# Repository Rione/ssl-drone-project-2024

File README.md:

# ssl-drone-project-2024

## branch tree
```
master{
    development{
        dp_KiCad{}
        dp_Fusion360{}
        dp_software{
            dp_stm32{}
            dp_esp32{}
        }
    }
}
```

Githubにコミットするときは基本的に``dp_*****``ブランチを選択

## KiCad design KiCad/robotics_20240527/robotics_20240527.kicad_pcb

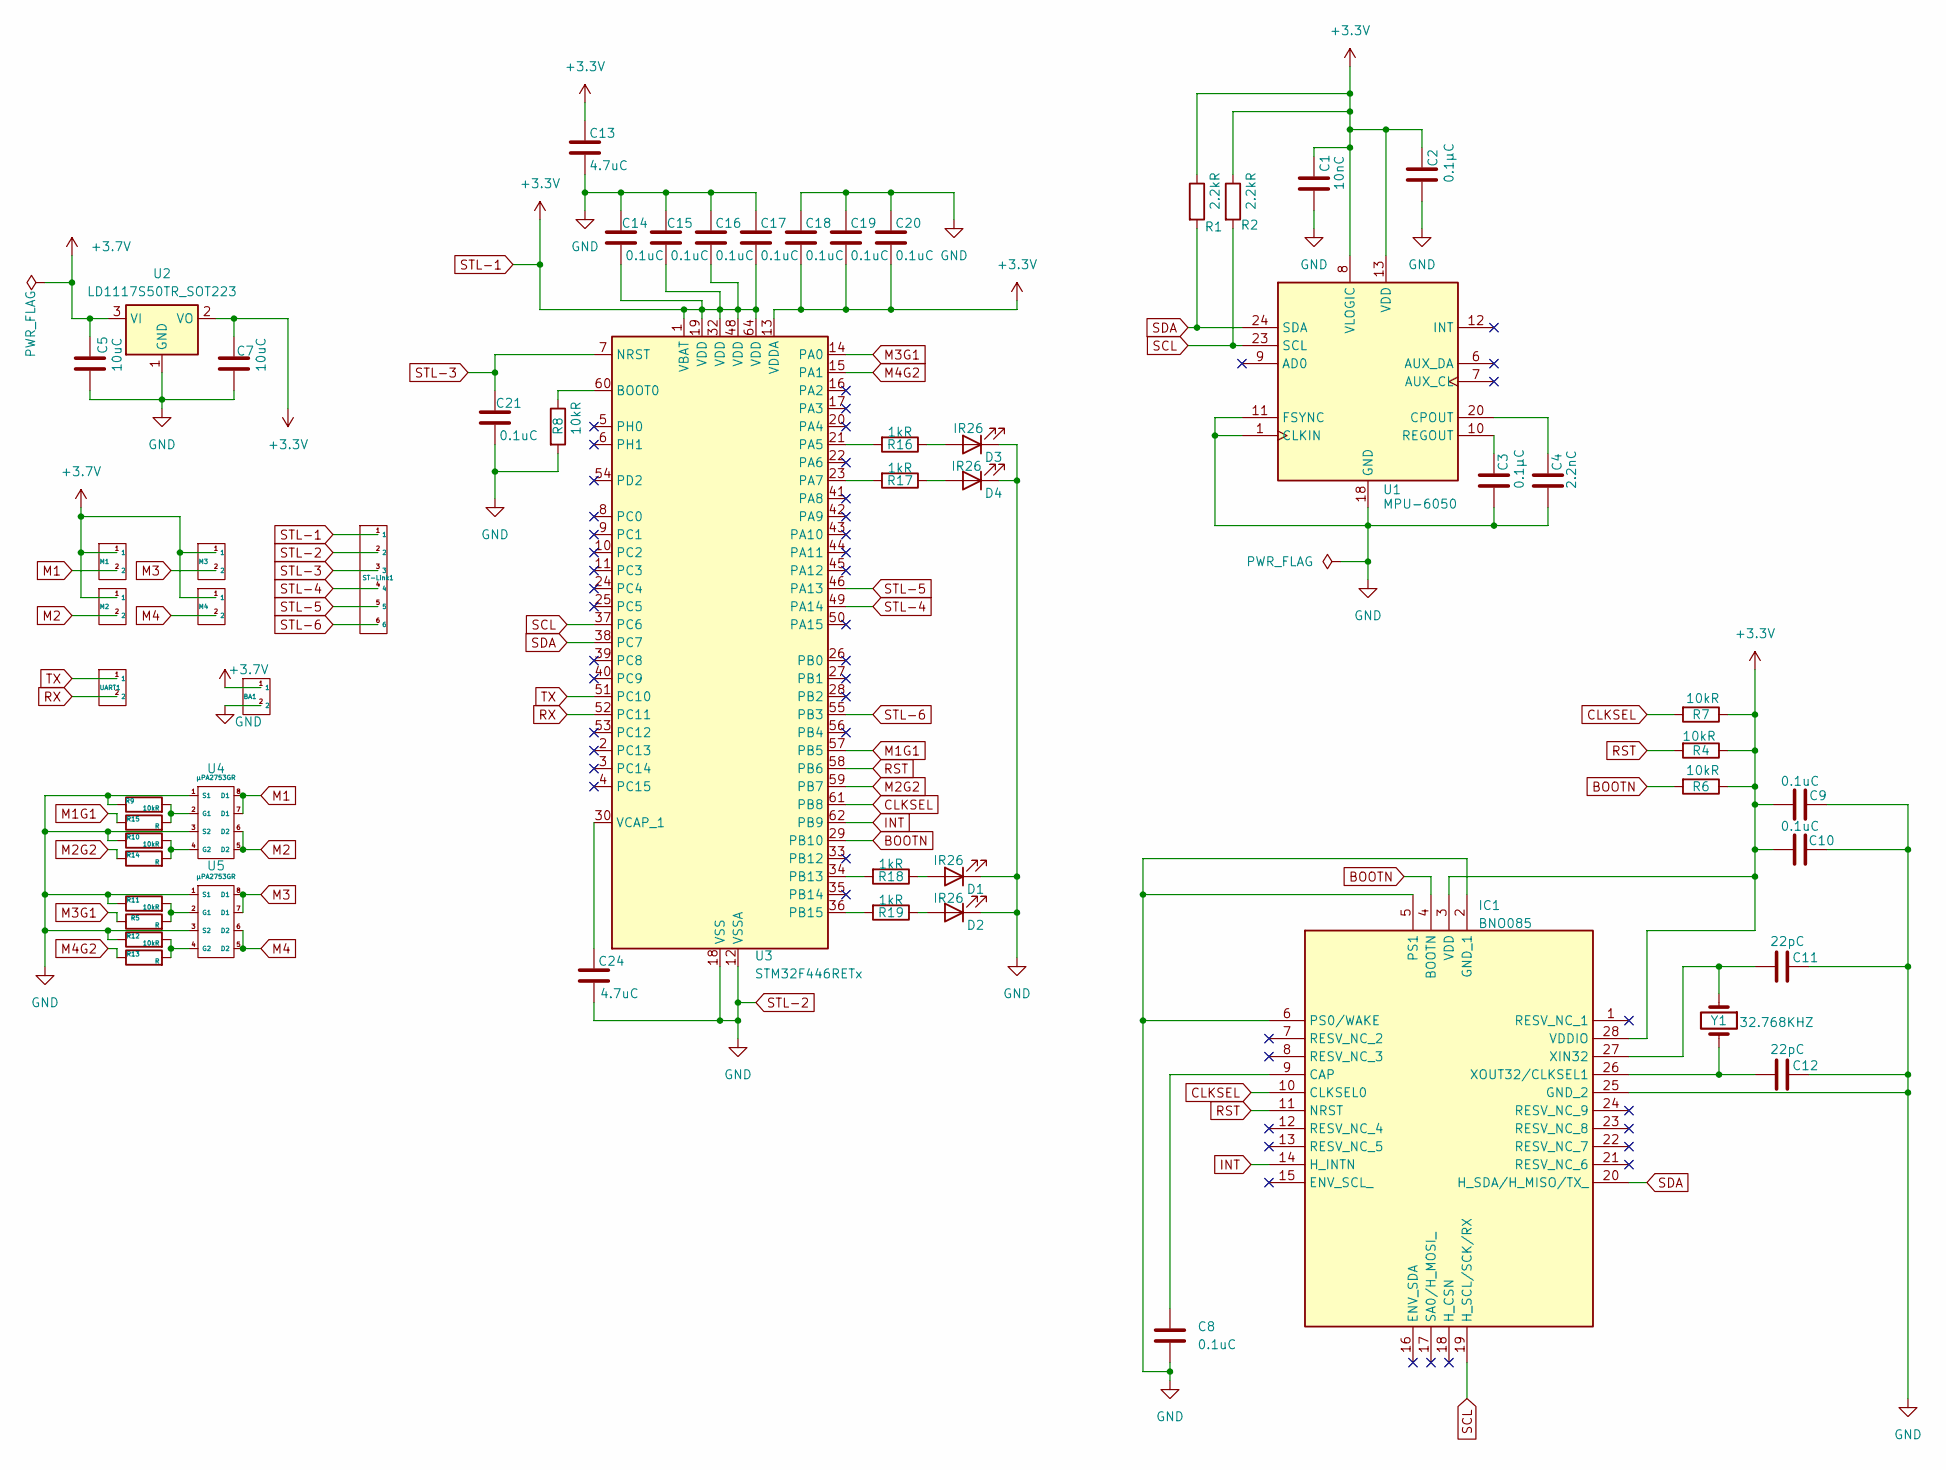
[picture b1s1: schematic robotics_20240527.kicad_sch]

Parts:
BA1: JST_PH_B2B-PH-K_1x02_P2.00mm_Vertical
C1: 10nC; C_0603_1608Metric_Pad1.08x0.95mm_HandSolder
C2, C3: 0.1µC; C_0603_1608Metric_Pad1.08x0.95mm_HandSolder
C4: 2.2nC; C_0603_1608Metric_Pad1.08x0.95mm_HandSolder
C5, C7: 10uC; C_0603_1608Metric_Pad1.08x0.95mm_HandSolder
C8, C9, C10, C14, C15, C16, C17, C18, C19, C20, C21: 0.1uC; C_0603_1608Metric_Pad1.08x0.95mm_HandSolder
C11, C12: 22pC; C_0603_1608Metric_Pad1.08x0.95mm_HandSolder
C13, C24: 4.7uC; C_0603_1608Metric_Pad1.08x0.95mm_HandSolder
D1, D2, D3, D4: IR26; LED_1206_3216Metric
IC1: BNO085; Mouser Part Number 526-BNO085
M1, M2, M3, M4: JST_PH_B2B-PH-K_1x02_P2.00mm_Vertical
R1, R2: 2.2kR; R_0603_1608Metric_Pad0.98x0.95mm_HandSolder
R4, R6, R7, R8, R9, R10, R11, R12: 10kR; R_0603_1608Metric_Pad0.98x0.95mm_HandSolder
R5, R13, R14, R15: R; R_0603_1608Metric_Pad0.98x0.95mm_HandSolder
R16, R17, R18, R19: 1kR; R_0603_1608Metric_Pad0.98x0.95mm_HandSolder
ST-Link1: JST_PH_S6B-PH-K_1x06_P2.00mm_Horizontal
U1: MPU-6050; InvenSense_QFN-24_4x4mm_P0.5mm
U2: LD1117S50TR_SOT223; SOT-223-3_TabPin2
U3: STM32F446RETx; LQFP-64_10x10mm_P0.5mm
U4, U5: μPA2753GR; HSOP-8-1EP_3.9x4.9mm_P1.27mm_EP2.3x2.3mm
UART1: JST_PH_B2B-PH-K_1x02_P2.00mm_Vertical
Y1: 32.768KHZ; Crystal_SMD_MicroCrystal_CC7V-T1A-2Pin_3.2x1.5mm_HandSolder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

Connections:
+3.7V: BA1.1, C5.1, M1.1, M2.1, M3.1, M4.1, U2.3 (VI)
BOOTN: IC1.4 (BOOTN), R6.2, U3.29 (PB10)
CLKSEL: IC1.10 (CLKSEL0), R7.2, U3.61 (PB8)
INT: IC1.14 (H_INTN), U3.62 (PB9)
M1: M1.2, U4.7 (D1), U4.8 (D1)
M1G1: R15.1, U3.57 (PB5)
M2: M2.2, U4.5 (D2), U4.6 (D2)
M2G2: R14.1, U3.59 (PB7)
M3: M3.2, U5.7 (D1), U5.8 (D1)
M3G1: R5.1, U3.14 (PA0)
M4: M4.2, U5.5 (D2), U5.6 (D2)
M4G2: R13.1, U3.15 (PA1)
unnamed: D1.2 (A), R18.1
unnamed: D2.2 (A), R19.1
unnamed: D3.2 (A), R16.1
unnamed: D4.2 (A), R17.1
unnamed: C8.1, IC1.9 (CAP)
unnamed: C11.2, IC1.27 (XIN32), Y1.1
unnamed: C12.2, IC1.26 (XOUT32/CLKSEL1), Y1.2
unnamed: C4.1, U1.20 (CPOUT)
unnamed: C3.1, U1.10 (REGOUT)
unnamed: R8.1, U3.60 (BOOT0)
unnamed: R16.2, U3.21 (PA5)
unnamed: R17.2, U3.23 (PA7)
unnamed: R18.2, U3.34 (PB13)
unnamed: R19.2, U3.36 (PB15)
unnamed: C24.1, U3.30 (VCAP_1)
unnamed: R9.2, R15.2, U4.2 (G1)
unnamed: R10.2, R14.2, U4.4 (G2)
unnamed: R5.2, R11.2, U5.2 (G1)
unnamed: R12.2, R13.2, U5.4 (G2)
RST: IC1.11 (NRST), R4.2, U3.58 (PB6)
RX: U3.52 (PC11), UART1.2
SCL: IC1.19 (H_SCL/SCK/RX), R2.2, U1.23 (SCL), U3.37 (PC6)
SDA: IC1.20 (H_SDA/H_MISO/TX_), R1.2, U1.24 (SDA), U3.38 (PC7)
STL-1: C1.1, C2.1, C7.1, C9.2, C10.2, C13.1, C14.2, C15.2, C16.2, C17.2, C18.2, C19.2, C20.2, IC1.3 (VDD), IC1.28 (VDDIO), R1.1, R2.1, R4.1, R6.1, R7.1, ST-Link1.1, U1.8 (VLOGIC), U1.13 (VDD), U2.2 (VO), U3.1 (VBAT), U3.13 (VDDA), U3.19 (VDD), U3.32 (VDD), U3.48 (VDD), U3.64 (VDD)
STL-2: BA1.2, C1.2, C2.2, C3.2, C4.2, C5.2, C7.2, C8.2, C9.1, C10.1, C11.1, C12.1, C13.2, C14.1, C15.1, C16.1, C17.1, C18.1, C19.1, C20.1, C21.2, C24.2, D1.1 (K), D2.1 (K), D3.1 (K), D4.1 (K), IC1.2 (GND_1), IC1.5 (PS1), IC1.6 (PS0/WAKE), IC1.25 (GND_2), R8.2, R9.1, R10.1, R11.1, R12.1, ST-Link1.2, U1.1 (CLKIN), U1.11 (FSYNC), U1.18 (GND), U2.1 (GND), U3.12 (VSSA), U3.18 (VSS), U3.31 (VSS), U3.47 (VSS), U3.63 (VSS), U4.1 (S1), U4.3 (S2), U5.1 (S1), U5.3 (S2)
STL-3: C21.1, ST-Link1.3, U3.7 (NRST)
STL-4: ST-Link1.4, U3.49 (PA14)
STL-5: ST-Link1.5, U3.46 (PA13)
STL-6: ST-Link1.6, U3.55 (PB3)
TX: U3.51 (PC10), UART1.1

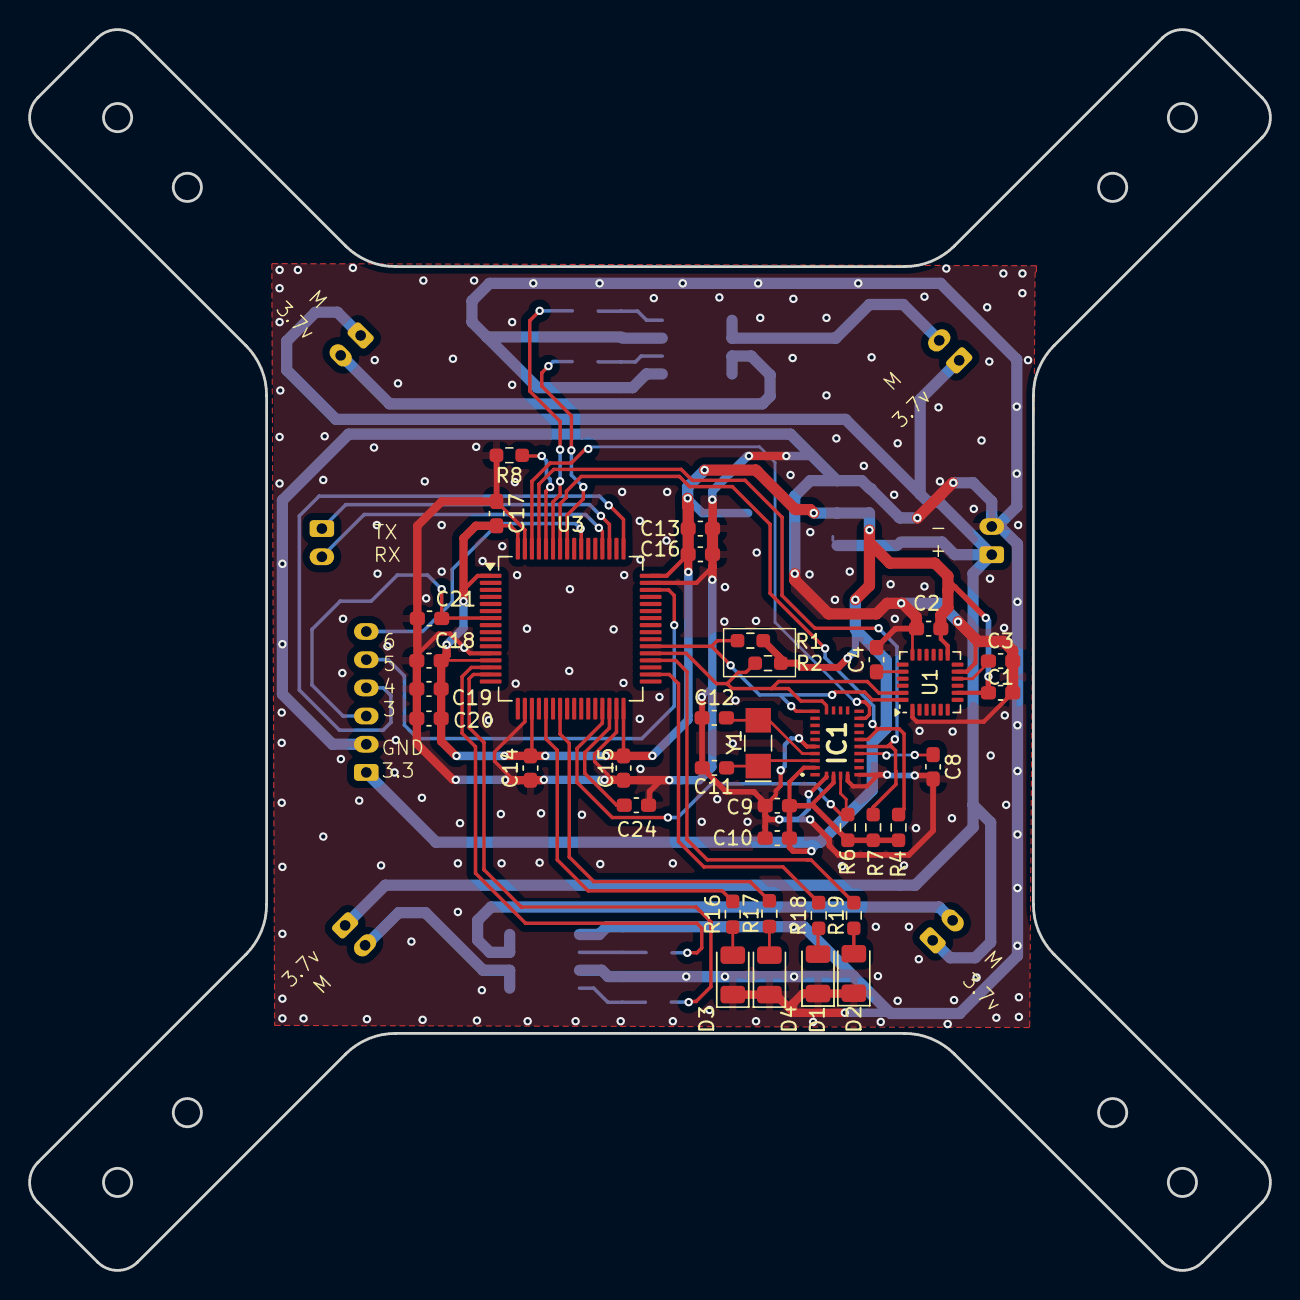
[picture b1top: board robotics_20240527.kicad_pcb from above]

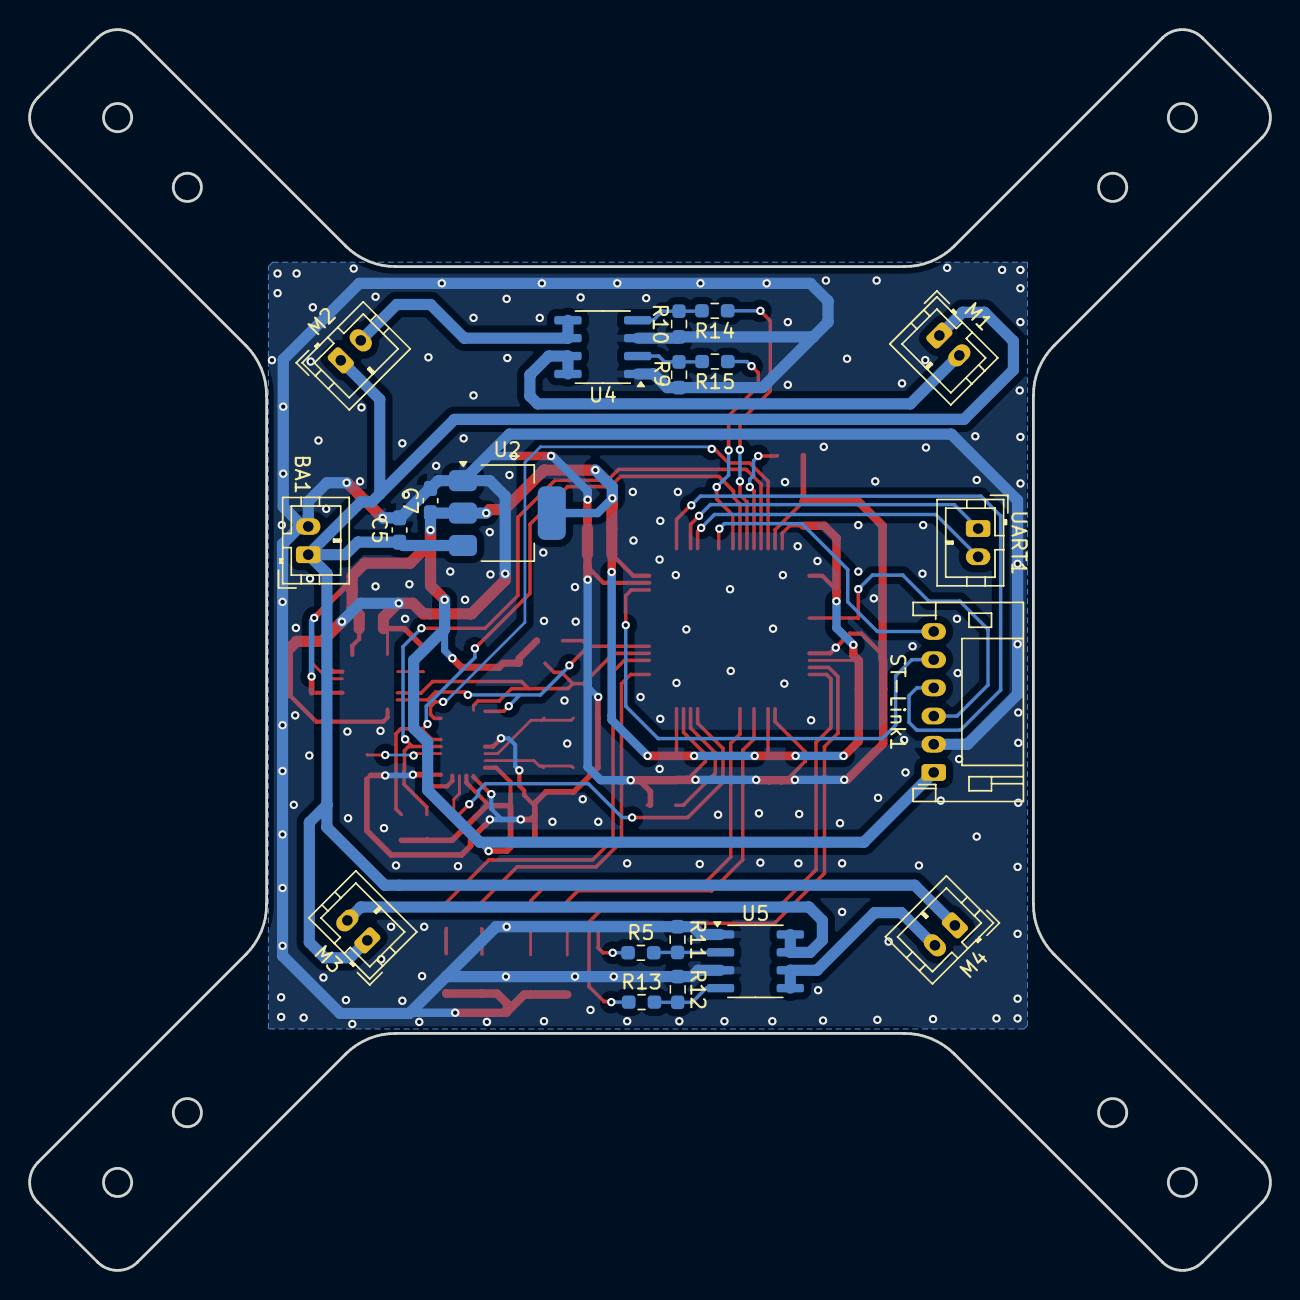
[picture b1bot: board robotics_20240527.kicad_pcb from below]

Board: 2 copper layers, 88.0 x 88.0 mm, 57 parts (20 on the bottom side), 42 nets.

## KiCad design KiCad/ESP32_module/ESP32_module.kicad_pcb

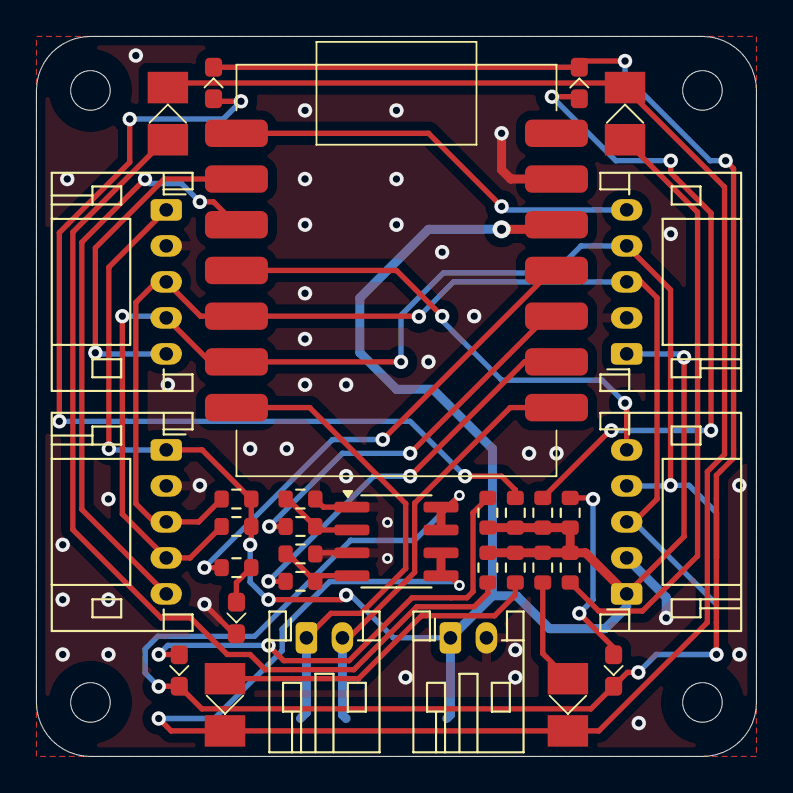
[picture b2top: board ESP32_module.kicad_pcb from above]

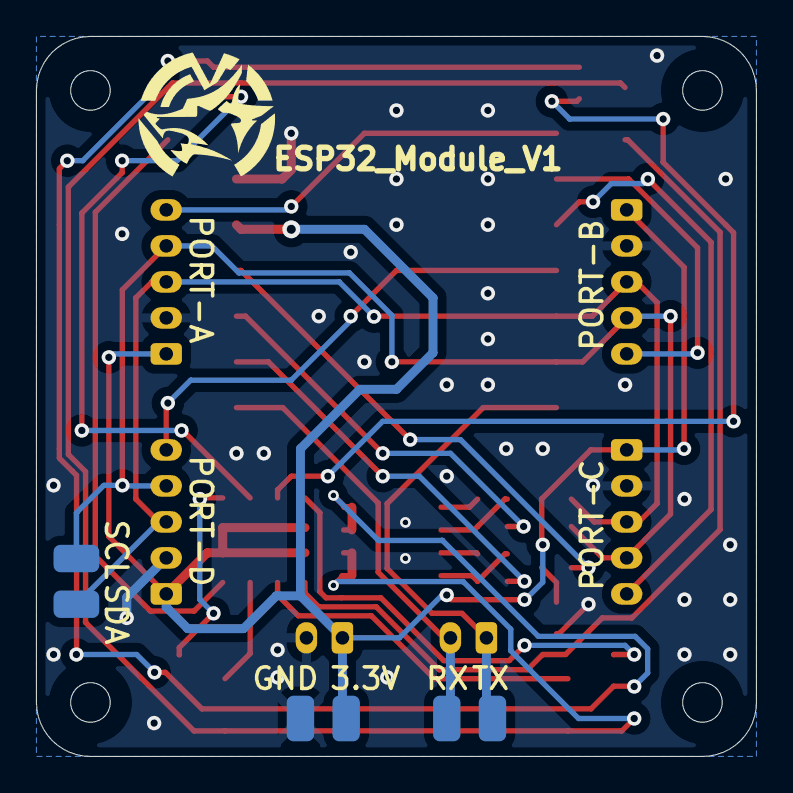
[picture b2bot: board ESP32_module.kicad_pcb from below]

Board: 2 copper layers, 40.0 x 40.0 mm, 35 parts (3 on the bottom side), 26 nets.

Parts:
D1, D6, D7, D8, D9: LED; D_0603_1608Metric_Pad1.05x0.95mm_HandSolder
D2, D3, D4, D5: LED; LEDM3528X190N
FET1: μPA2753GR; HSOP-8-1EP_3.9x4.9mm_P1.27mm_EP2.3x2.3mm
J1, J2, J3, J4: Conn_01x05_Pin; JST_PH_S5B-PH-K_1x05_P2.00mm_Horizontal
J5, J6: Conn_01x02_Pin; JST_PH_S2B-PH-K_1x02_P2.00mm_Horizontal
J7, J8, J9: Conn_01x02_Pin; 2.54mm_pin
M1: ESP32_XAIO; ESP32_XIAO
R1, R2: PU; R_0603_1608Metric
R3, R12, R13, R14, R15: 1k; R_0603_1608Metric
R4, R5: 400; R_0603_1608Metric
R6, R7: 10k; R_0603_1608Metric
R8, R9, R10, R11: 10; R_0603_1608Metric

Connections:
+3.3V: J1.1, J2.1, J3.1, J4.1, J6.1, J7.1, M1.3 (3.3V), R1.2, R2.2, R8.1, R9.1, R10.1, R11.1, R12.1, R13.1, R14.1, R15.1
/XSHOUT_A: J1.5, M1.8 (D0)
/XSHOUT_B: J2.5, M1.9 (D1)
/XSHOUT_C: J3.5, M1.10 (D2)
/XSHOUT_D: J4.5, M1.11 (D3)
GND1: D1.1 (K), FET1.1 (Source_1), FET1.3 (Source_2), J1.2, J2.2, J3.2, J4.2, J6.2, J7.2, M1.2 (GND), R6.2, R7.2
unnamed: D1.2 (A), R3.2
unnamed: D2.2 (A), R8.2
unnamed: D2.1 (K), D3.1 (K), D4.1 (K), D5.1 (K), FET1.5 (Drain_2), FET1.6 (Drain_2)
unnamed: D3.2 (A), R9.2
unnamed: D4.2 (A), R10.2
unnamed: D5.2 (A), R11.2
unnamed: D6.2 (A), R12.2
unnamed: D6.1 (K), D7.1 (K), D8.1 (K), D9.1 (K), FET1.7 (Drain_1), FET1.8 (Drain_1)
unnamed: D7.2 (A), R13.2
unnamed: D8.2 (A), R14.2
unnamed: D9.2 (A), R15.2
unnamed: FET1.2 (Gate_1), R4.2, R6.1
unnamed: FET1.4 (Gate_2), R5.2, R7.1
unnamed: M1.6 (D8), R5.1
unnamed: M1.5 (D9), R4.1
unnamed: M1.4 (D10), R3.1
RX: J5.2, J9.2, M1.7 (D7/RX)
SCL: J1.4, J2.4, J3.4, J4.4, J8.2, M1.13 (D5/SCL), R1.1
SDA: J1.3, J2.3, J3.3, J4.3, J8.1, M1.12 (D4/SDA), R2.1
TX: J5.1, J9.1, M1.14 (D6/TX)

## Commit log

2024-05-20 Add README.txt
2024-06-12 test
2024-06-12 test2
2024-07-03 Create test
2024-07-08 Build Successful "CameraWebServer"
    From Github https://github.com/limengdu/SeeedStudio-XIAO-ESP32S3-Sense-camera/tree/main/CameraWebServer
    Attention:
    Platformio's esp32 library is old and we can't use
    ledcAttach(LED_LEDC_CHANNEL, 5000, 8);
    Then it should be alter to
    ledcSetup(LED_LEDC_CHANNEL, 5000, 8);
2024-07-09 Running Successful
2024-08-22 Successful WiFi AP_mode
2024-08-22 fix WiFI power
2024-08-23 MPU6050、BNO085 途中
2024-08-31 add ESP32_module
2024-08-31 add I2C pullup resister
2024-08-31 add fet
2024-09-01 add PCB design
2024-09-01 Complite ESP32_module PCB design
2024-09-01 add 3D data
2024-09-10 fix mosfet
2024-09-18 fix gnd
2024-09-23 add pre_gui_test
2024-09-28 done common.css
2024-09-28 done mobile footer pre design
2024-10-01 done index.html
2024-10-02 add index.css
2024-10-03 add_stm_1
2024-10-04 fix index.css
2024-10-04 com p222
2024-10-21 add html
2024-10-21 fix html
2024-10-23 fix main.cpp
2024-10-26 add bno055 library
2024-10-27 done debug
2024-10-27 done debug2
2024-10-27 bno読めた
2024-10-27 yaw,pitch,rollが読めた
2024-10-27 PWM周波数変更
2024-10-27 done_P_CONTROL
2024-10-27 add_pid_library
2024-10-27 PDで姿勢制御
2024-10-27 PIDゲイン調整完
2024-10-27 Successful cam stream
2024-10-28 add gz file
2024-10-29 fix cam size
